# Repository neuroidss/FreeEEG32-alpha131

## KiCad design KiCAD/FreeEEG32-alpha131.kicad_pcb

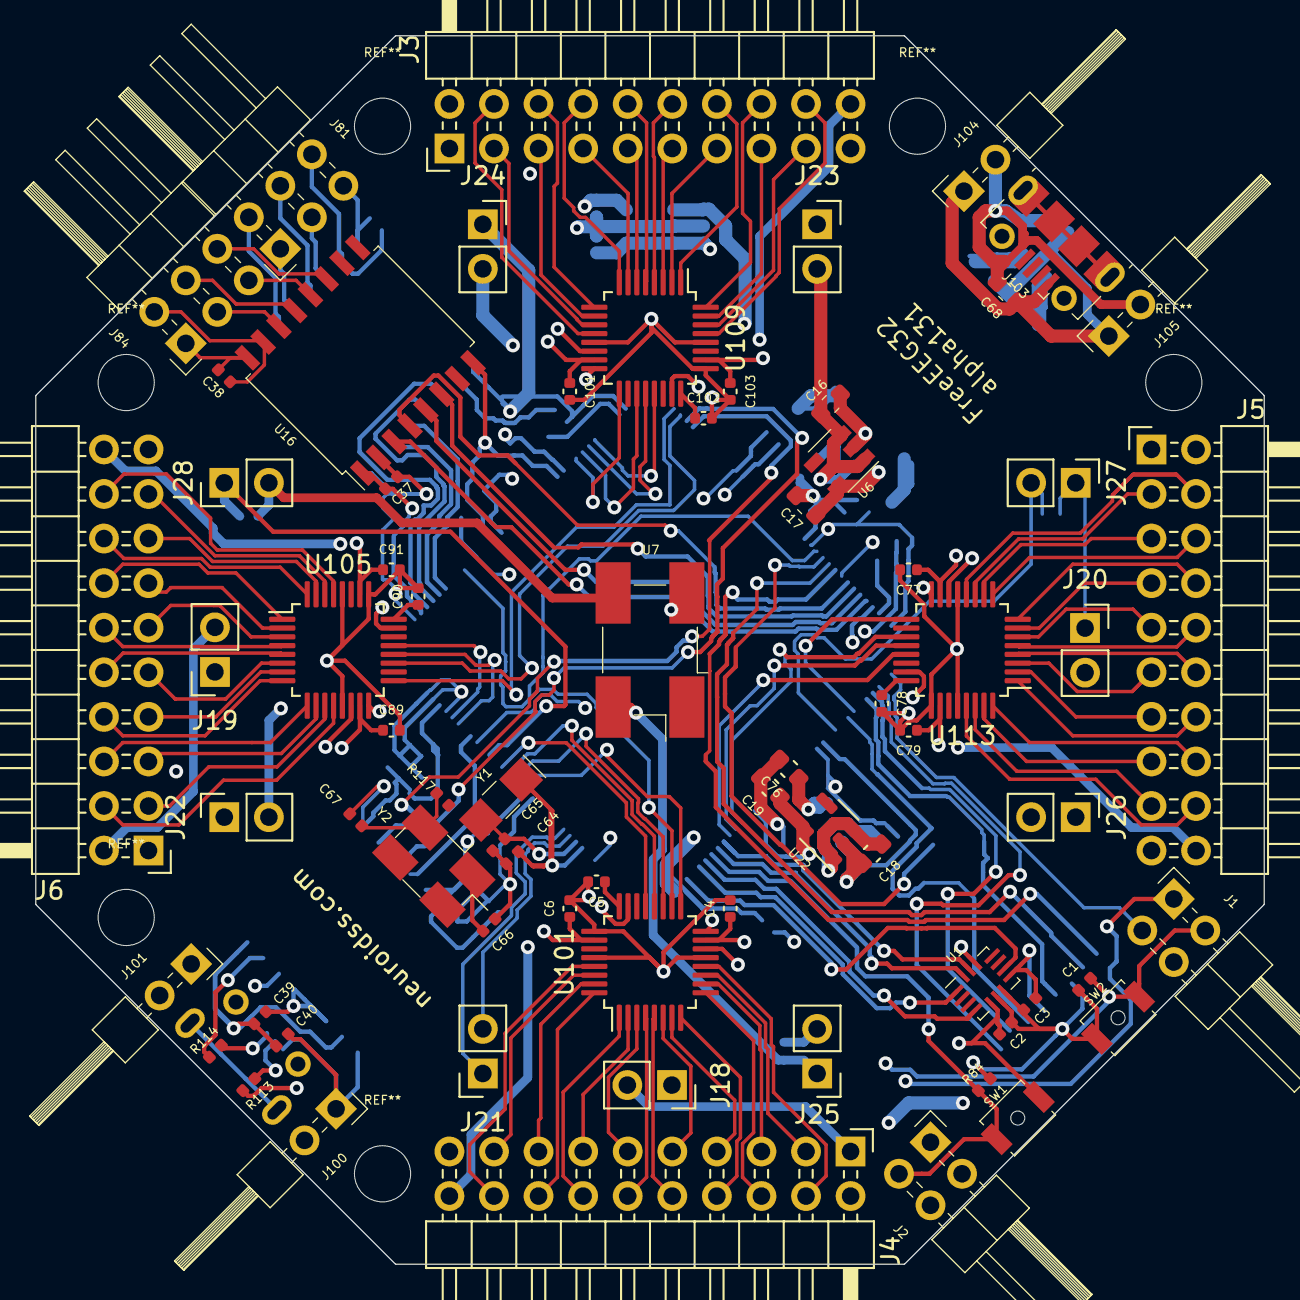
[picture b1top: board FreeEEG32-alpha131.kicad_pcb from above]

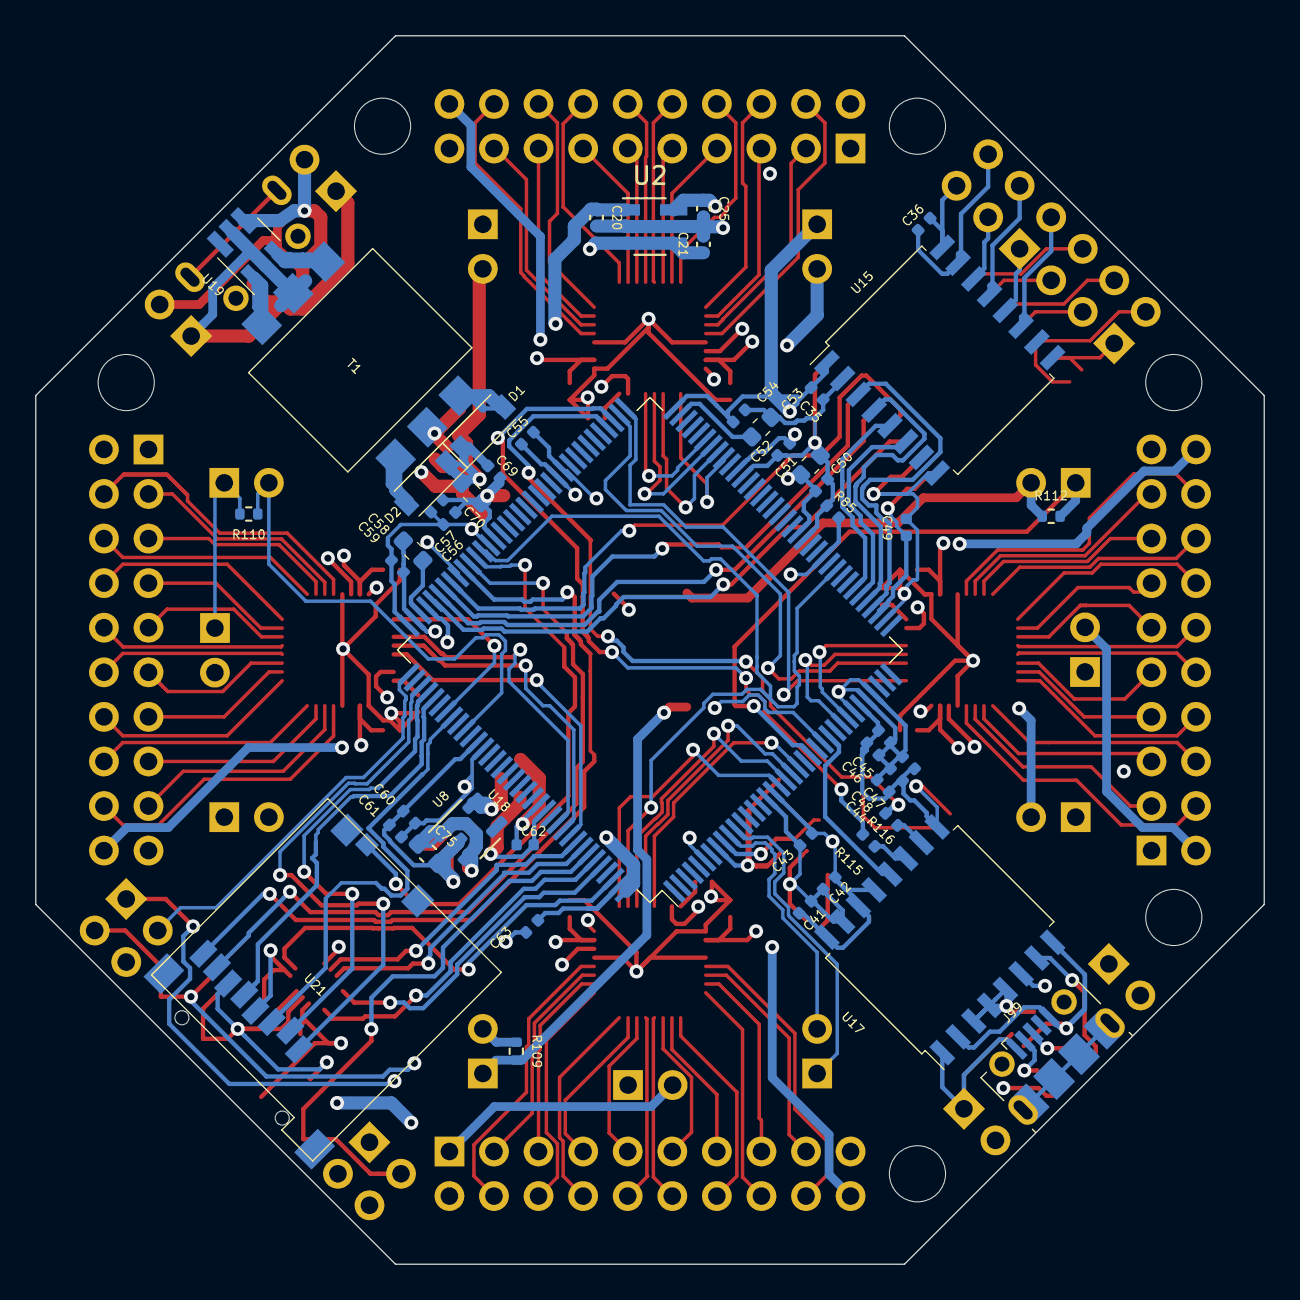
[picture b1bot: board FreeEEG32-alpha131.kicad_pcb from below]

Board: 4 copper layers, 70.0 x 70.0 mm, 118 parts (48 on the bottom side), 163 nets.

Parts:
C1, C2, C3, C20, C21, C25, C35, C36, C37, C38, C39, C40, C41, C42, C43, C44, C45, C47, C49, C50, C52, C54, C55, C56, C59, C60, C62, C63, C69: 100n; C_0402_1005Metric
C4, C6, C46, C48, C57, C61, C77, C79, C89, C91, C101, C103: 1u; C_0402_1005Metric
C5, C78, C90, C102: 220nF; C_0402_1005Metric
C16, C17, C18, C19, C53, C58, C75, C76: 2.2u; C_0603_1608Metric
C51: 4.7u; C_0603_1608Metric
C64, C66: CL1; C_0402_1005Metric
C65, C67: CL2; C_0402_1005Metric
C68, C70: 10u; C_0603_1608Metric
D1, D2: D_Schottky; D_SOD-123
J1, J2: Conn_02x02_Odd_Even; PinHeader_2x02_P2.54mm_Horizontal
J3, J4, J5, J6: Conn_02x10_Odd_Even; PinHeader_2x10_P2.54mm_Horizontal
J18, J19, J20, J21, J22, J23, J24: Conn_01x02; PinSocket_1x02_P2.54mm_Vertical
J25, J26, J27, J28: Conn_01x02; PinHeader_1x02_P2.54mm_Vertical
J81, J84: Conn_02x03_Odd_Even; PinHeader_2x03_P2.54mm_Horizontal
J99, J103: USB_B_Micro; USB_Micro-B_Molex-105017-0001
J100, J101, J104, J105: Conn_01x02; PinHeader_2x01_P2.54mm_Horizontal
R84, R85: 4k7; R_0402_1005Metric
R109, R110, R112: 0; R_0402_1005Metric
R113, R114, R115, R116: 24; R_0402_1005Metric
R117: R_EXT; R_0402_1005Metric
SW1, SW2: SW_Push; SW_SPST_B3U-1000P-B
T1: 750315371
U1: LSM6DS3; Bosch_LGA-14_3x2.5mm_P0.5mm
U2: REF2025; SOT-23-5_HandSoldering
U6, U8, U22: LP5907; SOT-23-5
U7: FXO-SM7_OSC-SMD7050_short; Oscillator_SMD_EuroQuartz_XO91-4Pin_7.0x5.0mm_HandSoldering
U15: ISO7341c; SOIC-16W_7.5x10.3mm_P1.27mm
U16: ADUM1402BRWZ; SOIC-16W_7.5x10.3mm_P1.27mm
U17: ADuM3160; SOIC-16W_7.5x10.3mm_P1.27mm
U18: STM32H743ZITx; LQFP-144_20x20mm_P0.5mm
U19: SN6505B; SOT-23-6_Handsoldering
U21: 473521001
U101, U105, U109, U113: ADS131M08IRSN; LQFP-32_5x5mm_P0.5mm
Y1: 32768Hz; Crystal_SMD_EuroQuartz_EQ161-2Pin_3.2x1.5mm_HandSoldering
Y2: 16MHz; Crystal_SMD_EuroQuartz_MJ-4Pin_5.0x3.2mm_HandSoldering

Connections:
/ADC1/24_CAP: C5.1, U101.24 (CAP)
/ADC5/24_CAP: C90.1, U105.24 (CAP)
/ADC9/24_CAP: C102.1, U109.24 (CAP)
/ADC13/24_CAP: C78.1, U113.24 (CAP)
/MCU/8_PC14: C64.1, U18.8 (PC14), Y1.1
/MCU/9_PC15: C65.1, U18.9 (PC15), Y1.2
/MCU/71_VCAP_1: C53.1, U18.71 (VCAP1)
/MCU/106_VCAP_2: C58.1, U18.106 (VCAP2)
ACC_1_SDO_SAO: U1.1 (SDO/SA0), U18.140 (PB9)
ACC_4_INT1: U1.4 (INT1), U18.139 (PB8)
ACC_6_GND: C1.1, C2.2, C3.2, C4.2, C5.2, C6.2, C16.2, C17.2, C18.2, C19.2, C20.2, C21.2, C25.2, C35.2, C37.2, C41.2, C42.2, C43.2, C44.2, C45.2, C46.2, C47.2, C48.2, C49.2, C50.2, C51.2, C52.2, C53.2, C54.2, C55.2, C56.2, C57.2, C58.2, C59.2, C60.2, C61.2, C62.2, C63.2, C64.2, C65.2, C66.2, C67.2, C69.2, C70.2, C75.2, C76.2, C77.2, C78.2, C79.2, C89.2, C90.2, C91.2, C101.2, C102.2, C103.2, J2.2, J3.19, J4.19, J5.19, J6.19, J22.1, J23.1, R84.2, R85.2, SW2.1, T1.5, U1.6 (GND), U1.7 (GND), U2.2 (GND), U6.2 (GND), U7.2 (GND), U8.2 (GND), U15.2 (GND1), U15.8 (GND1), U16.2 (GND1), U16.8 (GND1), U17.9 (GND2), U17.15 (GND2), U18.16 (VSS), U18.31 (VSSA), U18.38 (VSS), U18.51 (VSS), U18.61 (VSS), U18.83 (VSS), U18.94 (VSS), U18.107 (VSS), U18.120 (VSS), U18.130 (VSS), U21.6 (Vss), U22.2 (GND), U101.13 (AGND), U101.25 (DGND), U101.28 (AGND), U105.13 (AGND), U105.25 (DGND), U105.28 (AGND), U109.13 (AGND), U109.25 (DGND), U109.28 (AGND), U113.13 (AGND), U113.25 (DGND), U113.28 (AGND)
ACC_9_INT2: U1.9 (INT2), U18.142 (PE1)
ACC_12_CS: C2.1, C3.1, C19.1, C35.1, C37.1, C41.1, C42.1, C43.1, C44.1, C45.1, C46.1, C47.1, C48.1, C49.1, C50.1, C51.1, C52.1, C54.1, C55.1, C56.1, C57.1, C59.1, C60.1, C61.1, C62.1, C63.1, J2.1, J24.1, J25.2, R109.1, SW1.1, U1.5 (VDDIO), U1.8 (VDD), U1.12 (CS), U15.1 (VCC1), U16.1 (VCC1), U17.13 (SPD), U17.14 (VDD2), U17.16 (VBUS2), U18.6 (VBAT), U18.17 (VDD), U18.30 (VDD), U18.32 (VREF+), U18.33 (VDDA), U18.39 (VDD), U18.52 (VDD), U18.62 (VDD), U18.72 (VDD), U18.84 (VDD), U18.95 (VDD33_USB), U18.108 (VDD), U18.121 (VDD), U18.131 (VDD), U18.143 (PDR_ON), U18.144 (VDD), U21.4 (VDD), U22.5 (OUT)
ACC_13_SCL: U1.13 (SCL), U18.136 (PB6)
ACC_14_SDA: U1.14 (SDA), U18.137 (PB7)
ADC1_01_AIN2P: J4.14, U101.1 (AIN2P)
ADC1_02_AIN2N: J4.13, U101.2 (AIN2N)
ADC1_03_AIN3N: J4.11, U101.3 (AIN3N)
ADC1_04_AIN3P: J4.12, U101.4 (AIN3P)
ADC1_05_AIN4P: J4.10, U101.5 (AIN4P)
ADC1_06_AIN4N: J4.9, U101.6 (AIN4N)
ADC1_07_AIN5N: J4.7, U101.7 (AIN5N)
ADC1_08_AIN5P: J4.8, U101.8 (AIN5P)
ADC1_09_AIN6P: J4.6, U101.9 (AIN6P)
ADC1_10_AIN6N: J4.5, U101.10 (AIN6N)
ADC1_11_AIN7N: J4.3, U101.11 (AIN7N)
ADC1_12_AIN7P: J4.4, U101.12 (AIN7P)
ADC1_17_CS: U18.18 (PF6), U101.17 (CS)
ADC1_18_DRDY: U18.46 (PB0), U18.96 (PC6), U101.18 (DRDY)
ADC1_19_SCLK: U18.19 (PF7), U101.19 (SCLK)
ADC1_20_DOUT: U18.20 (PF8), U101.20 (DOUT)
ADC1_21_DIN: U18.21 (PF9), U101.21 (DIN)
ADC1_29_AIN0P: J4.18, U101.29 (AIN0P)
ADC1_30_AIN0N: J4.17, U101.30 (AIN0N)
ADC1_31_AIN1N: J4.15, U101.31 (AIN1N)
ADC1_32_AIN1P: J4.16, U101.32 (AIN1P)
ADC5_01_AIN2P: J6.14, U105.1 (AIN2P)
ADC5_02_AIN2N: J6.13, U105.2 (AIN2N)
ADC5_03_AIN3N: J6.11, U105.3 (AIN3N)
ADC5_04_AIN3P: J6.12, U105.4 (AIN3P)
ADC5_05_AIN4P: J6.10, U105.5 (AIN4P)
ADC5_06_AIN4N: J6.9, U105.6 (AIN4N)
ADC5_07_AIN5N: J6.7, U105.7 (AIN5N)
ADC5_08_AIN5P: J6.8, U105.8 (AIN5P)
ADC5_09_AIN6P: J6.6, U105.9 (AIN6P)
ADC5_10_AIN6N: J6.5, U105.10 (AIN6N)
ADC5_11_AIN7N: J6.3, U105.11 (AIN7N)
ADC5_12_AIN7P: J6.4, U105.12 (AIN7P)
ADC5_17_CS: U18.73 (PB12), U105.17 (CS)
ADC5_19_SCLK: U18.74 (PB13), U105.19 (SCLK)
ADC5_20_DOUT: U18.28 (PC2_C), U105.20 (DOUT)
ADC5_21_DIN: U18.29 (PC3_C), U105.21 (DIN)
ADC5_29_AIN0P: J6.18, U105.29 (AIN0P)
ADC5_30_AIN0N: J6.17, U105.30 (AIN0N)
ADC5_31_AIN1N: J6.15, U105.31 (AIN1N)
ADC5_32_AIN1P: J6.16, U105.32 (AIN1P)
ADC9_01_AIN2P: J3.14, U109.1 (AIN2P)
ADC9_02_AIN2N: J3.13, U109.2 (AIN2N)
ADC9_03_AIN3N: J3.11, U109.3 (AIN3N)
ADC9_04_AIN3P: J3.12, U109.4 (AIN3P)
ADC9_05_AIN4P: J3.10, U109.5 (AIN4P)
ADC9_06_AIN4N: J3.9, U109.6 (AIN4N)
ADC9_07_AIN5N: J3.7, U109.7 (AIN5N)
ADC9_08_AIN5P: J3.8, U109.8 (AIN5P)
ADC9_09_AIN6P: J3.6, U109.9 (AIN6P)
ADC9_10_AIN6N: J3.5, U109.10 (AIN6N)
ADC9_11_AIN7N: J3.3, U109.11 (AIN7N)
ADC9_12_AIN7P: J3.4, U109.12 (AIN7P)
ADC9_17_CS: U18.64 (PE11), U109.17 (CS)
ADC9_29_AIN0P: J3.18, U109.29 (AIN0P)
ADC9_30_AIN0N: J3.17, U109.30 (AIN0N)
ADC9_31_AIN1N: J3.15, U109.31 (AIN1N)
ADC9_32_AIN1P: J3.16, U109.32 (AIN1P)
ADC10_14_REFIN: C20.1, U2.1 (VBIAS), U101.14 (REFIN), U105.14 (REFIN), U109.14 (REFIN), U113.14 (REFIN)
ADC10_15_AVDD: C4.1, C17.1, C77.1, C89.1, C101.1, J3.20, J4.20, J5.20, J6.20, J24.2, U6.5 (OUT), U101.15 (AVDD), U105.15 (AVDD), U109.15 (AVDD), U113.15 (AVDD)
ADC10_16_SYNC/RESET: J20.1, J27.1, R110.2, U101.16 (SYNC/RESET), U105.16 (SYNC/RESET), U109.16 (SYNC/RESET), U113.16 (SYNC/RESET)
ADC10_19_SCLK: U18.65 (PE12), U109.19 (SCLK)
ADC10_20_DOUT: U18.66 (PE13), U109.20 (DOUT)
ADC10_21_DIN: U18.67 (PE14), U109.21 (DIN)
ADC10_23_XTAL1/CLKIN: U18.100 (PA8), U101.23 (XTAL1/CLKIN), U105.23 (XTAL1/CLKIN), U109.23 (XTAL1/CLKIN), U113.23 (XTAL1/CLKIN)
ADC10_26_DVDD: C6.1, C76.1, C79.1, C91.1, C103.1, J18.1, U8.5 (OUT), U101.26 (DVDD), U105.26 (DVDD), U109.26 (DVDD), U113.26 (DVDD)
ADC13_01_AIN2P: J5.14, U113.1 (AIN2P)
ADC13_02_AIN2N: J5.13, U113.2 (AIN2N)
ADC13_03_AIN3N: J5.11, U113.3 (AIN3N)
ADC13_04_AIN3P: J5.12, U113.4 (AIN3P)
ADC13_05_AIN4P: J5.10, U113.5 (AIN4P)
ADC13_06_AIN4N: J5.9, U113.6 (AIN4N)
ADC13_07_AIN5N: J5.7, U113.7 (AIN5N)
ADC13_08_AIN5P: J5.8, U113.8 (AIN5P)
ADC13_09_AIN6P: J5.6, U113.9 (AIN6P)
ADC13_10_AIN6N: J5.5, U113.10 (AIN6N)
ADC13_11_AIN7N: J5.3, U113.11 (AIN7N)
ADC13_12_AIN7P: J5.4, U113.12 (AIN7P)
ADC13_17_CS: U18.115 (PD1), U113.17 (CS)
ADC13_19_SCLK: U18.133 (PB3), U113.19 (SCLK)
ADC13_20_DOUT: U18.134 (PB4), U113.20 (DOUT)
ADC13_21_DIN: U18.135 (PB5), U113.21 (DIN)
ADC13_29_AIN0P: J5.18, U113.29 (AIN0P)
ADC13_30_AIN0N: J5.17, U113.30 (AIN0N)
ADC13_31_AIN1N: J5.15, U113.31 (AIN1N)
ADC13_32_AIN1P: J5.16, U113.32 (AIN1P)
AINREF+: J3.2, J4.2, J5.2, J6.2, J19.2
AINREF-: J3.1, J4.1, J5.1, J6.1, J18.2
AVDD_1_IN: C16.1, C18.1, C21.1, C69.1, C70.1, C75.1, D1.1 (K), D2.1 (K), J2.4, J23.2, U2.3 (EN), U2.4 (VIN), U6.1 (IN), U6.3 (EN), U8.1 (IN), U8.3 (EN), U22.1 (IN), U22.3 (EN)
CRYSTAL_3_OUT: J28.2, R112.1, U7.3 (OUT)
CRYSTAL_4_Vin: J25.1, R109.2, U7.4 (Vin)
ISO_SPI_3_INA: U15.3 (INA), U18.40 (PA4)
ISO_SPI_4_INB: U15.4 (INB), U18.41 (PA5)
ISO_SPI_5_INC: U15.5 (INC), U18.43 (PA7)
ISO_SPI_6_OUTD: U15.6 (OUTD), U18.42 (PA6)
ISO_SPI_11_IND: J81.2, U15.11 (IND)
ISO_SPI_12_OUTC: J81.1, U15.12 (OUTC)
ISO_SPI_13_OUTB: J81.4, U15.13 (OUTB)
ISO_SPI_14_OUTA: J81.3, U15.14 (OUTA)
ISO_SPI_15_GND2: C36.2, J81.6, U15.15 (GND2)
ISO_SPI_16_VCC2: C36.1, J81.5, U15.16 (VCC2)
ISO_UART_3_INA: U16.3 (INA), U18.104 (PA12)
ISO_UART_4_INB: U16.4 (INB), U18.101 (PA9)
ISO_UART_5_OUTC: U16.5 (OUTC), U18.103 (PA11)
ISO_UART_6_OUTD: U16.6 (OUTD), U18.102 (PA10)
ISO_UART_11_IND: J84.6, U16.11 (IND)
ISO_UART_12_INC: J84.5, U16.12 (INC)
ISO_UART_13_OUTB: J84.4, U16.13 (OUTB)
ISO_UART_14_OUTA: J84.3, U16.14 (OUTA)
ISO_UART_15_GND2: C38.2, J84.2, U16.15 (GND2)
ISO_UART_16_VCC2: C38.1, J84.1, U16.16 (VCC2)
ISO_USB_1_VBUS1: C40.1, J99.1 (VBUS), J100.1, U17.1 (VBUS1)
ISO_USB_2_GND1: C39.2, C40.2, J99.5 (GND), J100.2, U17.2 (GND1), U17.8 (GND1)
ISO_USB_3_VDD1: C39.1, U17.3 (VDD1), U17.4 (PDEN), U17.5 (SPU)
ISO_USB_6_UD–: J99.2 (D-), J101.2, R113.2
ISO_USB_7_UD+: J99.3 (D+), J101.1, R114.2
ISO_USB_10_DD+: R116.1, U18.76 (PB15)
ISO_USB_11_DD–: R115.1, U18.75 (PB14)
ISO_USB_12_PIN: U17.12 (PIN), U18.26 (PC0)
MCU_10_PF0_I2C2_SDA: J21.2, U18.10 (PF0)
MCU_11_PF1_I2C2_SCL: J21.1, U18.11 (PF1)
MCU_23_RCC_OSC_IN: J19.1, J28.1, R112.2, U18.23 (PH0)
MCU_25_NRST: C1.2, J1.2, SW2.2, U18.25 (NRST)
MCU_48_PB2_BOOT1: J1.1, R85.1, U18.48 (PB2)
MCU_97_PC7_SDMMC1_DETECT: U18.97 (PC7), U21.9 (DETECT)
MCU_98_PC8_SDMMC1_D0: U18.98 (PC8), U21.7 (DATA0)
MCU_99_PC9_SDMMC1_D1: U18.99 (PC9), U21.8 (DATA1)
MCU_105_PA13_SYS_JTMS-SWDIO: J1.4, U18.105 (PA13)
MCU_109_PA14_SYS_JTCK-SWCLK: J1.3, U18.109 (PA14)
MCU_111_PC10_SDMMC1_D2: U18.111 (PC10), U21.1 (DATA2)
MCU_112_PC11_SDMMC1_D3: U18.112 (PC11), U21.2 (DATA3)
MCU_113_PC12_SDMMC1_CK: U18.113 (PC12), U21.5 (CLK)
MCU_116_PD2_SDMMC1_CMD: U18.116 (PD2), U21.3 (CMD)
MCU_118_PD4_ADC1_SYNC/RESET: J27.2, R110.1, U18.118 (PD4)
MCU_138_BOOT0: J2.3, R84.1, SW1.2, U18.138 (BOOT0)
unnamed: C66.1, Y2.1
unnamed: C67.1, R117.2, Y2.2
unnamed: D1.2 (A), T1.6
unnamed: D2.2 (A), T1.4
unnamed: R113.1, U17.6 (UD–)
unnamed: R114.1, U17.7 (UD+)
unnamed: R115.2, U17.11 (DD–)
unnamed: R116.2, U17.10 (DD+)
unnamed: T1.1, U19.3 (D2)
unnamed: T1.3, U19.1 (D1)
POWER_1_GND: C68.1, J103.5 (GND), J104.2, J105.2, U19.4 (GND)
POWER_2_VCC: C68.2, J103.1 (VBUS), J104.1, J105.1, T1.2, U19.2 (VCC), U19.5 (EN)
VREF_5_VREF: C25.1, J22.2, U2.5 (VREF)

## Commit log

2021-09-13 add all
2021-09-13 add out zip
2021-09-13 add out images
2022-05-05 16ch->4ch
